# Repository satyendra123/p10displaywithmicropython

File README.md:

# p10displaywithmicropython
i have micropython library and code for display the p10 display data

https://www.instructables.com/Arduino-UNO-Based-HUB75-LED-DISPLAY-DRIVER/ is link me jayenge to hume sara ka sara pcb mil jayega. hume us pcb ke gerber file lekr send kar dena hai pcb designing ke liye. aur isme isne khud ka library banaaya hai p10 hub75 rgb display ke liye.

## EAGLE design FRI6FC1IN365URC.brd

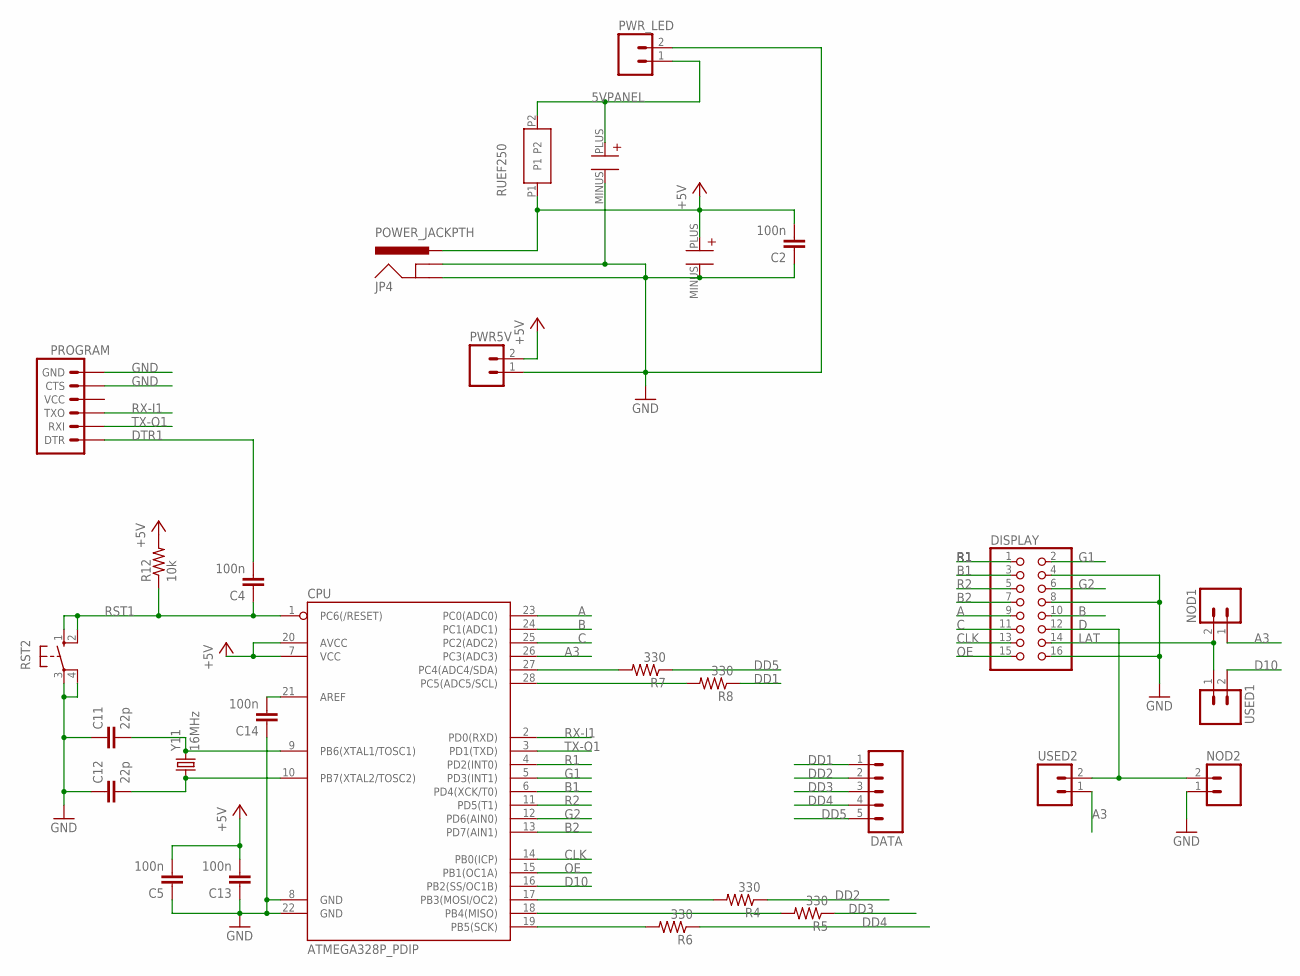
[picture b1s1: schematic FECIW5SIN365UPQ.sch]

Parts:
C1, C7: EEU-FR1C471B
C2, C4, C5, C13, C14: 100n; C025-024X044
C11, C12: 22p; C025-024X044
CPU: ATMEGA328P_PDIP; DIL28-3
DATA: M05PTH; 1X05
DISPLAY: PINHD-2X8; 2X08
JP4: POWER_JACKPTH; POWER_JACK_PTH
NOD1, NOD2: M02PTH; 1X02
PROGRAM: ARDUINO_SERIAL_PROGRAMPTH; 1X06
PWR5V: M02PTH; 1X02
PWR_LED: M023.5MM; SCREWTERMINAL-3.5MM-2
R4, R5, R6, R7, R8: 330; AXIAL-0.3
R12: 10k; AXIAL-0.3
RST2: 10-XX; B3F-10XX
RUEF250: RUEF250U
USED1, USED2: M02PTH; 1X02
Y11: 16MHz; HC49US

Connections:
5VPANEL: C7.PLUS, PWR_LED.1, RUEF250.P2
+5V: C1.PLUS, C2.2, C5.2, C13.2, CPU.7 (VCC), CPU.20 (AVCC), JP4.PWR, PWR5V.2, R12.P$2 (2), RUEF250.P1
A: CPU.23 (PC0(ADC0)), DISPLAY.9
A3: CPU.26 (PC3(ADC3)), NOD1.1, USED2.1
B: CPU.24 (PC1(ADC1)), DISPLAY.10
B1: CPU.6 (PD4(XCK/T0)), DISPLAY.3
B2: CPU.13 (PD7(AIN1)), DISPLAY.7
C: CPU.25 (PC2(ADC2)), DISPLAY.11
CLK: CPU.14 (PB0(ICP)), DISPLAY.13
D: DISPLAY.12, NOD2.2, USED2.2
D10: CPU.16 (PB2(SS/OC1B)), USED1.2
DD1: DATA.1, R8.P$1 (1)
DD2: DATA.2, R4.P$1 (1)
DD3: DATA.3, R5.P$1 (1)
DD4: DATA.4, R6.P$1 (1)
DD5: DATA.5, R7.P$1 (1)
DTR1: C4.2, PROGRAM.1 (DTR)
G1: CPU.5 (PD3(INT1)), DISPLAY.2
G2: CPU.12 (PD6(AIN0)), DISPLAY.6
GND: C1.MINUS, C2.1, C5.1, C7.MINUS, C11.1, C12.1, C13.1, C14.1, CPU.8 (GND), CPU.22 (GND), DISPLAY.4, DISPLAY.8, DISPLAY.16, JP4.GND, JP4.GNDBREAK, NOD2.1, PROGRAM.5 (CTS), PROGRAM.6 (GND), PWR5V.1, PWR_LED.2, RST2.3, RST2.4 (P1)
LAT: DISPLAY.14, NOD1.2, USED1.1
unnamed: C11.2, CPU.9 (PB6(XTAL1/TOSC1)), Y11.2
unnamed: C12.2, CPU.10 (PB7(XTAL2/TOSC2)), Y11.1
unnamed: CPU.19 (PB5(SCK)), R6.P$2 (2)
unnamed: CPU.18 (PB4(MISO)), R5.P$2 (2)
unnamed: CPU.17 (PB3(MOSI/OC2)), R4.P$2 (2)
unnamed: CPU.27 (PC4(ADC4/SDA)), R7.P$2 (2)
unnamed: CPU.28 (PC5(ADC5/SCL)), R8.P$2 (2)
unnamed: C14.2, CPU.21 (AREF)
OE: CPU.15 (PB1(OC1A)), DISPLAY.15
R1: CPU.4 (PD2(INT0)), DISPLAY.1
R2: CPU.11 (PD5(T1)), DISPLAY.5
RST1: C4.1, CPU.1 (PC6(/RESET)), R12.P$1 (1), RST2.1 (S), RST2.2 (S1)
RX-I1: CPU.2 (PD0(RXD)), PROGRAM.3 (TXO)
TX-O1: CPU.3 (PD1(TXD)), PROGRAM.2 (RXI)

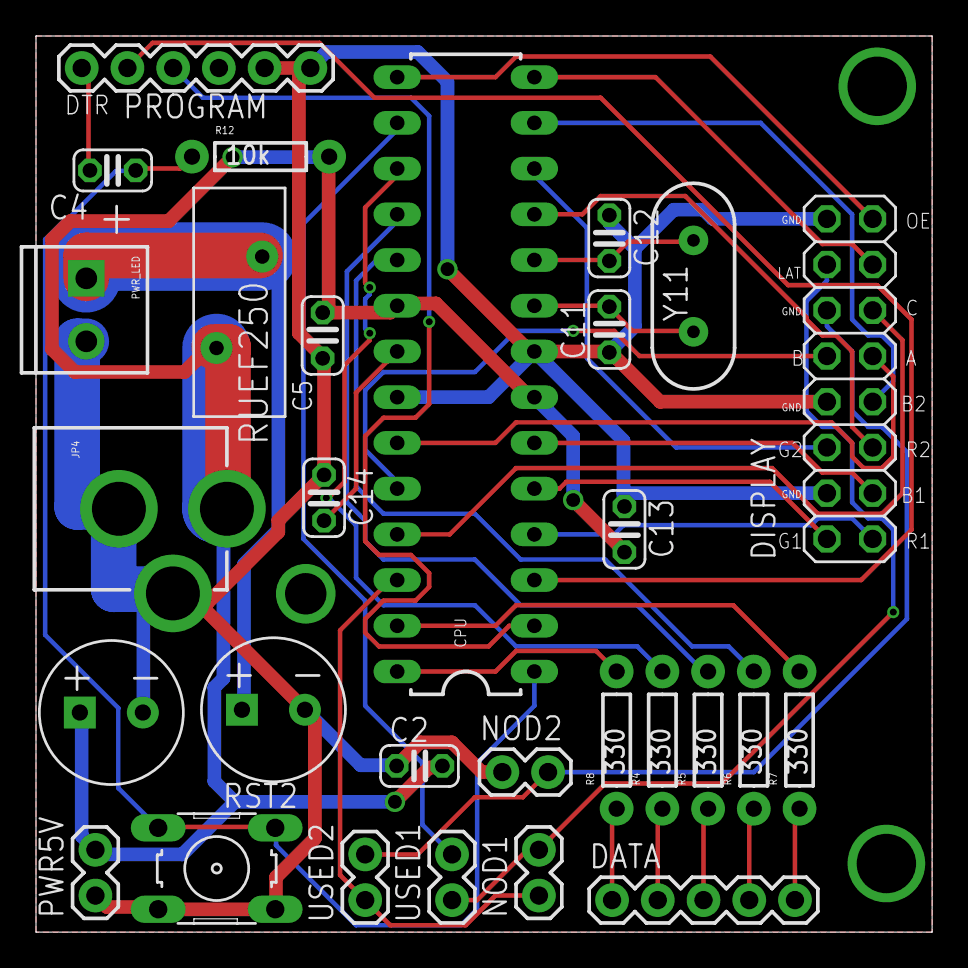
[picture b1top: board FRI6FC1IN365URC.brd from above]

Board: 2 copper layers, 49.8 x 49.8 mm, 29 parts (0 on the bottom side), 35 nets.

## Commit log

2024-06-06 Create p10displaymicropythonhub12

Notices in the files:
parts and their libraries:
SparkFun-FreqCtrl: Licensing: Creative Commons ShareAlike 4.0 International - https://creativecommons.org/licenses/by-sa/4.0
